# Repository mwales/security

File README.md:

# security
ctf, binary utils, debugging, notes

## ctf

Various writeups

* See outputJudge in utils folder for a utility for CTF challenge authors

## utils

* aesSource : I implemented AES from source (and by lookup table).  Wanted a
  better understanding of how it worked and stuff for when I perform Reverse
  Engineering steps.

* caesar : A tool I created to help me solve caesar ciphers

* entropy : Two python utilities that were posted on the internet (not my own
  source) for determing entropy of a file (and a good indicator if a file is
  compressed or encrypted).  I realized after making this, binwalk has a -E 
  filename option that is great, graphs entropy and everything.

* FindFloats : Tool that will take raw hex, ignores extra non-hex characters,
  and dumps out all the possible values the hex could be converted to.  For
  instance, the hex below contained a constant of pi in it

* hex2bin : Converts a hex file (or standard input) into binary output (sends
  the output to stdout, so redirect it into a file if it is a non-ASCII hex.

* largest_block_size : If you have a bunch of files and you want to find out
  what is the largest block size that all the files could be evenly divided
  with.  (I have no idea why I created this...)

* outputJudge : Script that CTF challenge authors / or teachers can use
  to give to students for them to evaluate their programs output.

* ReverseCRC : Tool that will brute force determine all the possible CRC-8
  and CRC-16 seed values for an arbitrary blob of hexadecimal data.

* simpleFileEncryption : Makes is easy to use OpenSSL to encrypt files.
  Behaves like a copy command for a single file at a time.  Works on both
  Linux and Windows.

* xorFiles : xor the contents of 2 files into each other

* Can dump flash from a U-Boot serial terminal.  Takes advantage of U-Boot
  CRC command to validate the data as it is downloaded to eliminate bit
  errors in transfer.

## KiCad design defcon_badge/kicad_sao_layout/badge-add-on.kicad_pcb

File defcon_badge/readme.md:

# Badge and SAO Demo

# Arduino Notes

Downloaded and extracted arduino_cli from github

https://github.com/arduino/arduino-cli/releases/download/0.25.1/arduino-cli_0.25.1_Linux_64bit.tar.gz

~/apps/arduino-cli core install arduino:avr

arduino-cli board list

~/apps/arduino-cli core install arduino:avr

~/apps/arduino-cli board attach -p /dev/ttyACM0 sao_badge

arduino_cli compile sao_badge

# Build and Run
~/apps/arduino-cli compile sao_badge && ~/apps/arduino-cli upload sao_badge

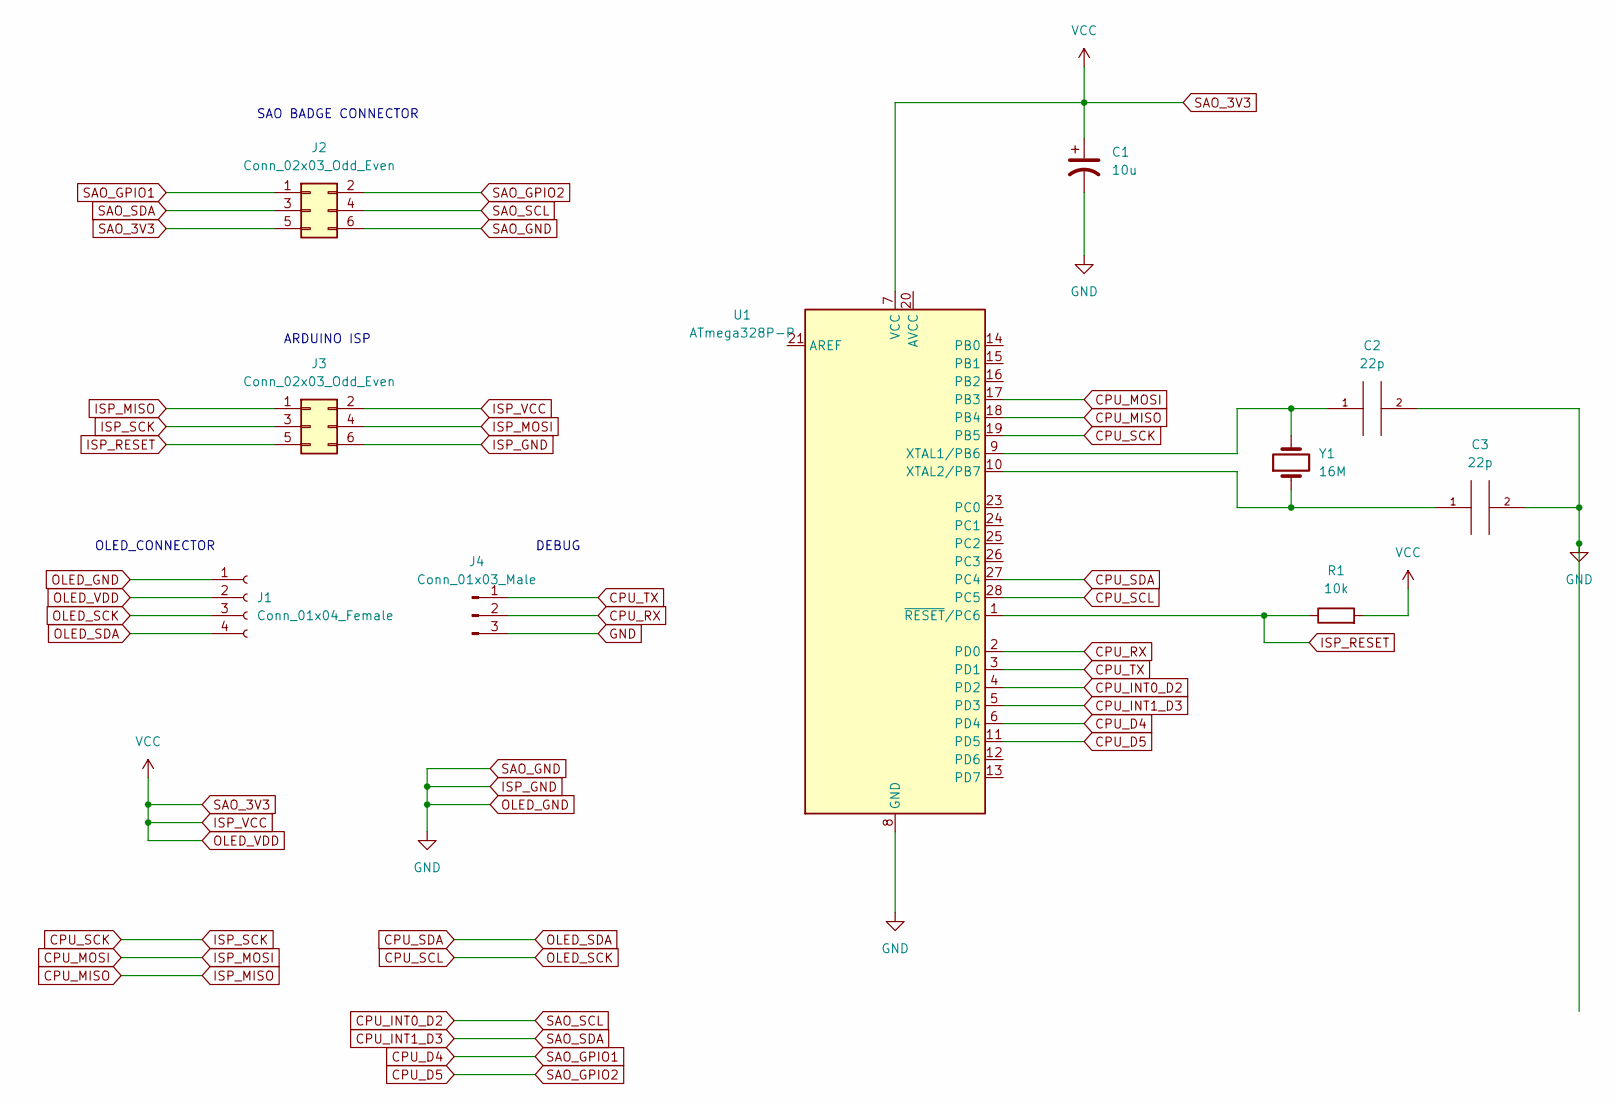
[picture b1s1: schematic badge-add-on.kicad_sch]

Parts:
C1: 10u; CP_Radial_D5.0mm_P2.50mm
C2, C3: 22p; C_Disc_D5.1mm_W3.2mm_P5.00mm
J1: Conn_01x04_Female; PinSocket_1x04_P2.54mm_Vertical
J2, J3: Conn_02x03_Odd_Even; PinSocket_2x03_P2.54mm_Vertical
J4: Conn_01x03_Male; PinSocket_1x03_P2.54mm_Vertical
R1: 10k; R_Axial_DIN0207_L6.3mm_D2.5mm_P15.24mm_Horizontal
U1: ATmega328P-P; DIP-28_W7.62mm
Y1: 16M; Resonator-2Pin_W10.0mm_H5.0mm

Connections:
CPU_D4: J2.1, U1.6 (PD4)
CPU_D5: J2.2, U1.11 (PD5)
CPU_INT0_D2: J2.4, U1.4 (PD2)
CPU_INT1_D3: J2.3, U1.5 (PD3)
CPU_MISO: J3.1, U1.18 (PB4)
CPU_MOSI: J3.4, U1.17 (PB3)
CPU_RX: J4.2, U1.2 (PD0)
CPU_SCK: J3.3, U1.19 (PB5)
CPU_SCL: J1.3, U1.28 (PC5)
CPU_SDA: J1.4, U1.27 (PC4)
CPU_TX: J4.1, U1.3 (PD1)
GND: C1.2, C2.2, C3.2, J1.1, J2.6, J3.6, J4.3, U1.8 (GND), U1.22 (GND)
ISP_RESET: J3.5, R1.1, U1.1 (~RESET/PC6)
ISP_VCC: C1.1, J1.2, J2.5, J3.2, R1.2, U1.7 (VCC)
unnamed: C2.1, U1.9 (XTAL1/PB6), Y1.2
unnamed: C3.1, U1.10 (XTAL2/PB7), Y1.1

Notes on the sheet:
OLED_CONNECTOR
SAO BADGE CONNECTOR
DEBUG
ARDUINO ISP

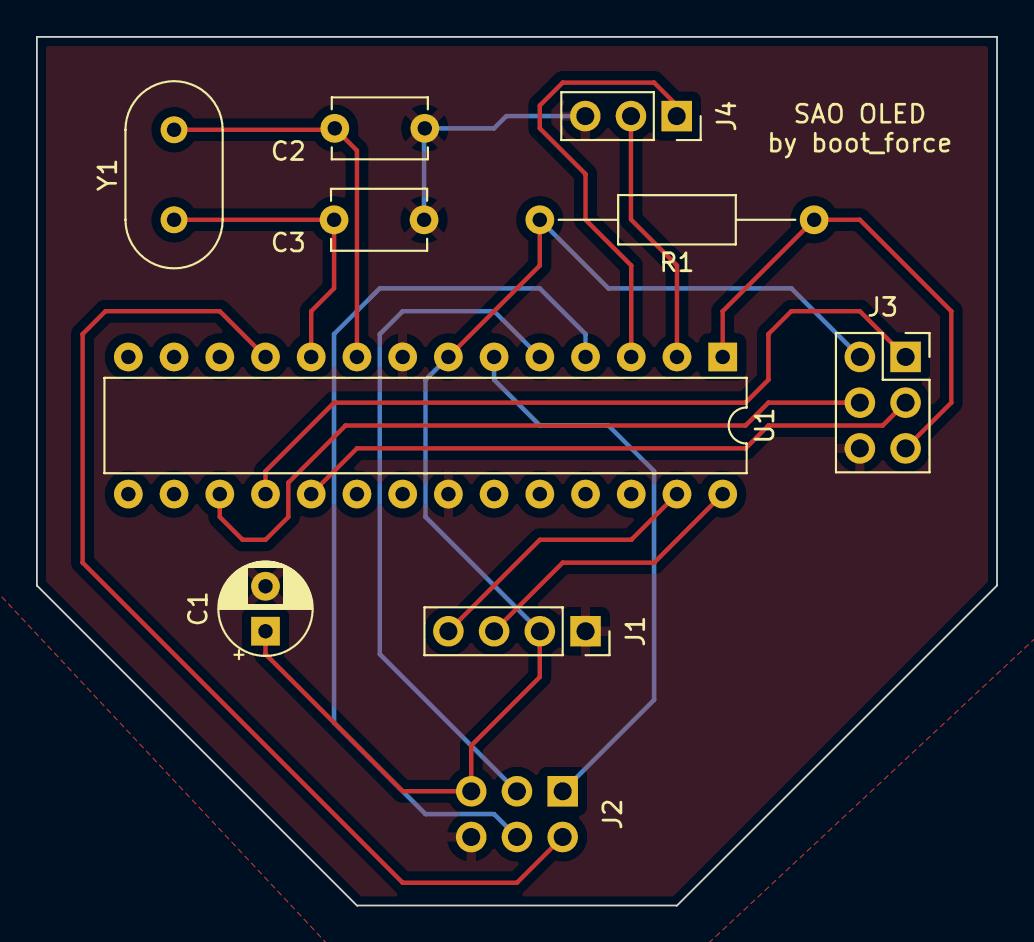
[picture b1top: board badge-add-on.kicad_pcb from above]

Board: 2 copper layers, 53.3 x 48.3 mm, 10 parts (1 on the bottom side), 16 nets.

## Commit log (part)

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2016-09-17 Moved stuff related to security from my notes repo this one
2016-09-17 Moving ctf stuff in education repo to security repo
2016-09-17 Moving security related stuff from utils repo to security repo
2016-09-17 Solution to first Tokyo Western 2016 problem
2016-09-17 Reverse_box write up completed
2016-09-17 Updating formatting
2016-09-17 Cleaned up python code a bit
2016-11-24 More notes about security and reversing
2016-12-13 Added some notes on x86 LEA instruction for future reference
2016-12-13 Copying a list of good CTF challenges from a pastebin
2016-12-31 33C3 Smartfridge complete
2016-12-31 More updates to the smartfridge writeup
2016-12-31 Tweaking markdown syntax
2016-12-31 Completed the smartfridge2 challenge
2017-01-04 More cleanup of client
2017-01-11 Working on my first IDA script, finding big headaches
2017-01-12 More progress, had to use the hexrays plugin to help with the analysis
2017-01-13 Got the function naming disovery working, and have a list of suggested function names
    Need to implement the naming, and add in some GUI enhancements still
2017-01-13 Discovered the bug in my results message box
2017-01-14 Adding a user interface to my function renaming script for IDA Pro
2017-01-15 Function name deconfliction added
2017-01-15 Core functionality complete
2017-01-15 Cleaned up the code, script output a bit
2017-01-16 Fixed some bugs, wasn't working correctly in IDA 64-bit
2017-01-27 Small utility to tell me largest block size for a file
2017-01-27 Added some notes in the source about what I want to add to the block size utility to make it useful for analyzing binaries.
2017-02-07 Alex 2016 Writeups
2017-02-07 Changed name of writeup to readme.md
    Now it will show up by default on github.com
2017-02-07 Minor formatting mods
2017-02-09 Have most of solution for OTP problem, want to fine tune it and clean it up now
2017-02-09 Alex CTF was in 2017, not 2016
2017-02-09 Made solution for the One Time Pad problem
2017-02-09 Added OTP to my writeup text
2017-02-09 Adjusted a link on writeup
2017-02-09 Added sample run of one time pad program
2017-02-14 NullCon CTF terrible writeup of shame
2017-02-20 Caesar cipher tool
2017-03-02 Log manipulation utility
2017-03-04 Short writeup of sorts for a fun Hack Center problem
2017-03-04 Created a utility to xor 2 files together
2017-03-04 Some more writeups on HackCenter enigma 2017 CTF
2017-05-02 Working on PicoCTF as I learn pwntools
2017-05-03 Another PicoCTF challenge implemented with pwn tools
2017-05-06 Created a ASLR defeating script for Plaid CTF challenge from 2013
2017-05-10 Function renamer IDA script will not stop on decompilation errors
2017-05-11 Made some improvements into my parsing of functions and arguements, still not great though
2017-05-12 func_renamer.py does a better job of finding associated string for a parameter
2017-05-12 func_renamer will try to rename returnType class::method(param, ...) style trace statements correctly
2017-05-21 Working on Blast Processing. QEMU manager for distributed tasks
2017-05-26 Need to move project to laptop, commit of crap in progress
2017-05-26 Microcorruption stuff i forgot to commit, no idea how far i got on this either
2017-05-27 Disk can now be selected, stored in a settings file so only have to enter once
2017-05-28 JSON parsed the greeting structure
2017-05-29 Basic emulator control working (stop, start, continue)
2017-05-29 Added emulator quit, and controlled cleanup of threads and processes
2017-06-01 Added screenshot feature
2017-06-05 This commit is a work in progress
2017-06-06 Added the ability to send human command interface commands via QMP
    For the BlastProcessing application
2017-06-09 Blast Processing: Updated QEMU screen
    - Added configuration controls (no code behind them yet)
    - Prettied the controls up
2017-06-13 Big BlastProcessing refactoring
    * Getting ready to add the ability to save and load QEMU config from files
    * Created a standalone QEMU configuration object to help
    * Still need to add some stuff to the QEMU configuration
    ** Port forward destinations
    ** Starting port number
2017-06-14 Blast Processing networking configuration
    * Can now specify up to 6 port forwards
    * Can specify the start port for port enumeration
    * Builds the command line with the port forwards instead of hardcoded ones
    * Builds the command with the correct network adapter
2017-06-15 Blast processing QEMU configuration implementation
    * Implemented VGA adapter and VNC settings
    * Configuration stuff left to do:
    ** Optical drive
    ** Freeform options
2017-06-16 Blast Processing configuration GUI done
    * Added the free form options
    * All options can be saved and loaded from text file
2017-06-19 Blast Processing buttons now work for selecting drive files
2017-06-25 Blast Processing. Started working on the ability to run many applications at one time.
2017-06-25 Blast processor now looping and using multiple cores
2017-06-28 Updated the Runner status GUI, simplified
2017-07-09 Can load and save Blast Processing configuration
2017-07-12 QemuRunner can not actually start multiple instances of QEMU at once
2017-07-28 Committing before I leave on vacation
2017-08-23 Created AES from source (only 128 bit key expansion works right now)
2017-08-29 Added inverse MixColumns to AES source. Not tested
2017-11-09 Adding easy to use encryption scripts
2017-11-09 More notes about using GDB
2017-11-16 Added IDA 6.95 installation notes for Linux
2017-11-29 Updated the debug printing to use a conditionally compiled style
2017-11-29 More debugging enhancements
2017-11-29 Added some file entropy calculation tools
2017-12-10 CTF failure leads to the creation of the worlds worst fuzzer
2018-01-14 SimpleGC I worked on for 34C3 2017
2018-01-16 Fixing some PyQt signal slot code written by an ignoramus
2018-01-16 IDA script to name functions of a Linux kernel based on the System.map file
2018-01-19 Changed the name of the QemuRunner class to BPRunner
2018-01-19 Some change I had laying around on the drive, want to refactory and split this tool
2018-01-19 Breaking Blast Processing into separate tools
2018-01-19 Started to fork Blast Processing application from the QemuConfigTool application
2018-01-22 Updated the tool to work on files that have different sizes (just warns you now)
2018-01-22 Partial writeup of incomplete CTF challenge
2018-01-22 Adding a file and a link to my own tool
2018-01-22 Fixing link in readme
2018-02-13 Added note about entropy tool in binwalk
2018-06-07 Working on a tool to import, export, and merge IDA Pro IDBs (and hopefully Binary Ninja databases as well.
2018-06-20 More work on IDA import / export tool
2018-10-19 Updated my gdb notes with new learnings...
2018-11-30 Added FindFloats reversing utility
2018-11-30 Fix type in README
2018-12-01 Adding cmake file
2018-12-06 Added CRC reversing tool. Works on CRC-8, need to add CRC-16
2018-12-07 Added CRC-16 support and tested Reverse CRC tool
2018-12-29 Trying to reverse some code that used the stat structure
2018-12-29 Added hex to offset output of the stat structure
2019-01-01 IDA script to dump the contents of a function into a file
2019-01-02 IDA script for dumping function update
    * Dump the bytes after the function, before the next function (has
    immediate values)
2019-01-03 IDA Script: Data Dump
    Lets user easily dump portion of binary to an external file
2019-01-04 Learning how to use Unicorn. ARM 3DS FTPD project
2019-01-04 Some code cleanup on my first unicorn project
2019-01-16 xxd annoyed me, wrote a better hex2binary tool
2019-01-16 Simple file encryption explicitly using md5 for password hashing. I think they changed newer versions of OpenSSL
2019-01-16 Added some more notes about how OpenSSL enc encrypts
2019-01-17 Updated the readme with the explanation of how OpenSSL derives key and IV for enc
2019-03-07 Started work on porting my function trace renaming script from IDA Pro to Ghidra
2019-03-09 Bunch of work done on trace renaming script, the end is in sight
2019-03-10 Ghidra renaming functions script complete. Needs cleanup now.
2019-03-11 Cleaned up Ghidra script (removed debug logs)
2019-05-06 Utility to mount disk and partitions on Linux
2019-05-17 Crediting the ghidra issue that has all the URLs for processor manuals
2019-05-19 git housekeping in the ctf directory
2019-05-19 Git housecleaning. xor util cleanup
2019-05-19 Git housecleaning. Adding build scripts to projects
2019-05-19 git housecleaning. hex2bin util cleanup
2019-08-15 Updated my simple file encryption utility to use pbkdf2 and sha512
2020-03-04 Tweak ghidra function naming script
2020-04-13 Added program that can turn U-Boot md.b data dump into binary
2020-04-16 Working on interactive U-Boot memory dumper. * GUI pretty much done * Can open serial port, get data, send data * Need to integrate with standalone dumper * Need to add CRC checking
2020-04-18 Interactive U-Boot dumper can generate dump commands and process data
2020-04-19 Funcitonally works
2020-04-19 Finished the U-Boot dumper
2020-06-14 Older version of Qt don't have back() method
2020-06-14 Update label when dump is completed
2020-06-15 Doesn't work on Telo because it doesn't have WD
2020-08-13 Added SH4 manual link
2021-08-12 Dumping bug fix, and no CRC command will skip CRC state machine steps now
2022-04-15 Worked on Space Heroes CTF Vader Challenge
2022-04-15 Adding gitignore to the last commit
2022-04-20 House cleaning in CTF folder
2022-04-20 CTF readme created
2022-04-20 Core file notes
2022-04-20 Upated SpaceHeroes vader solve with simpler rop script
2022-04-20 TAMU CTF 22 writeups.
    Team BootForce scores 700 pts for 141st place. Slava Ukraini!
2022-05-20 Found an update for hex2bin that I just had laying around in my git folder
2022-05-29 Adding some notes about how to use Docker to execute CTF challenge
2022-05-30 Commiting an old CTF solve I worked on
2022-08-02 Trying to make a badge add-on for defcon
2022-08-03 Finished badge add on hardware design and sent gerbers to PCB fab
2022-08-06 Programming defcon arduino
2022-08-07 SAO software complete
2022-08-22 GDB note that I forgot to commit from a long time ago
2022-08-22 Rough draft of notes for badge puzzles
2022-08-24 worked more on defcon badge writeup
2022-08-24 renaming the writeup for github default preview
2022-09-09 Updating DEFCON 30 badge writeup, still not complete
2022-09-09 Minor documentation updates
2022-09-13 Updating DEFCON 30 badge challenge writeup
    Finished documenting solution for chal 1
2022-09-13 Cleaning up some markdown in security readme
2022-09-18 Worked a little bit more on the defcon 30 badge writeup
2022-09-19 Defcon 30 Badge RE writeup complete
2022-10-01 DownUnderCTF baby arx solution
2022-10-03 Writeup on DUCTF22 source-provided rev challenge
2022-10-31 Writeup for one of the chals from Blue Hen Univ Deleware CTF
2022-10-31 Wordle solutions from Blue Hen / Univ Delaware CTF
2022-10-31 wordle challenge dad mode writeup added
2022-11-02 Intro 2 challenge and writeup
2022-11-02 Solution for bluehen pwn intro1
2022-11-02 Writeup of intro 1 completed
2022-11-07 Updated notes
2023-04-04 RitSec23 chals I completed
2023-04-04 Scripts for setup CTF VM
2023-04-14 QEMU chroot notes
2023-05-03 Fixing md errors in my ritsec writeup
2023-06-29 Updated IDA Pro func renamer scripts
    * Unfucked all the whitespace
    * Updated so that it worked on 1 test file I threw at it with IDA v8.2
2023-06-29 Buf fixes for IDA func_renamer script
2023-07-17 Adding note about creating structs in Binja programatically
2023-08-24 Added badge video
2023-09-29 Solution and Writeup for ViewSource CTF 2023 Reverse/x0rr3al challenge. 122 solves
2024-03-17 Program to fix endianness in binaries
2025-01-21 Copied script I'm using in Wildcat CTF to judge students program output
2025-01-21 Updated main readme with new utility
2025-01-22 Updating readme with how outputJudge program works
2025-03-18 Solutions to various PicoCTF 2025 challenges I got around to trying out
2025-05-22 Binja snippet to identify most called functions
